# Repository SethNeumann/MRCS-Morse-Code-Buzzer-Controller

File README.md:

# REPO NAME: MRCS-Morse-Code-Buzzer-Controller
## License: Creative Commons Attribution-NonCommercial-ShareAlike

On many operations-oriented model railroads, particularly those which use time-table and train-order (TT&TO) or tower-based dispatching, 
there is a need to provide telephone communications between the dispatcher and the agent/operators. However, even on large model railroads
with multiple agent/operators, the physical distances between the operator positions are often insufficient to allow the operators to
reliably determine that “hey that’s my phone ringing.”

The Morse Code Buzzer Controller serves up to seven stations, tapping out each ringing station's Telegraph call sign in Railroad Morse.
An additional output can be designated an “ambience” buzzer that will randomly play one of several canned messages. These could be train
orders, news reports, or “inside jokes”

The board accepts push button inputs, stops when the phone goes off-hook (phone must have a suitable contact to provide an isolated ground 
or use the MRCS Off-Hook_Detector) and can drive loads of up to 0.5 Amp at up to 48 Volts DC.  All buzzer/sounder devices must use the same
supply.  Sounders must have have a coil resistance of greater than 40 ohms if using a 12V supply, or else use our Sounder Driver.

This version accepts 10-24 VDC from the MRCS telephone bus or a layout auxilliary supply or an external wall wart (not supplied)

The on-board Arduino Pro-Mini runs the "station buzzers" sketch by Steve Williams.  Please indicate the telegraph codes for your 
stations, unless you intend to load the sketch yourself.

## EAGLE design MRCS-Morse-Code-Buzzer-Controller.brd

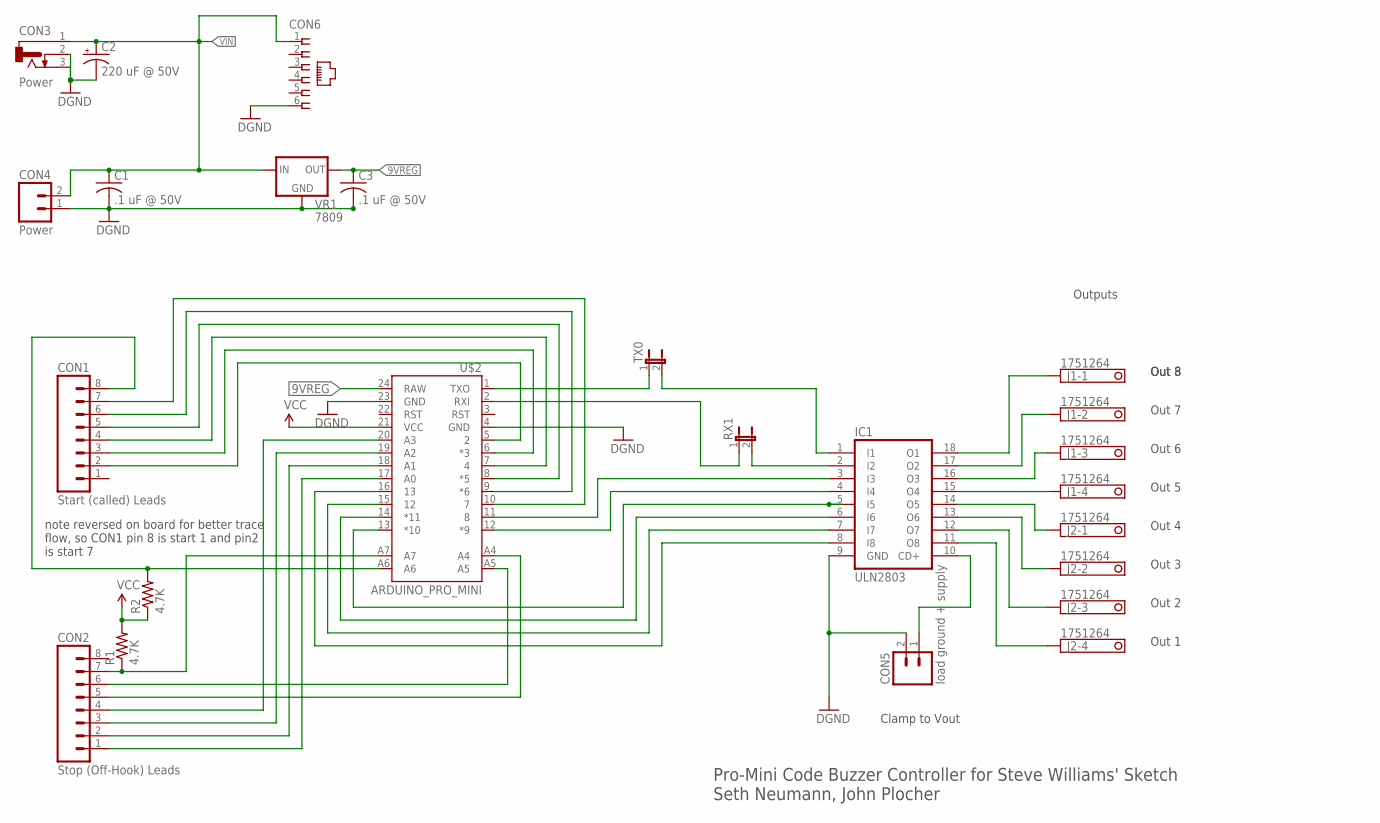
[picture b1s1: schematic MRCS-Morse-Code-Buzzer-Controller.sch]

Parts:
C1, C3: .1 uF @ 50V; C025-030X050
C2: 220 uF @ 50V; E3,5-10
CON1: Start (called) Leads; 1X08_LOCK
CON2: Stop (Off-Hook) Leads; 1X08_LOCK
CON3: Power; DCJ0202
CON4: Power; MSTB2
CON5: load ground + supply; MSTB2
CON6: CONNECTOR-RJ25-43860-2-MOLEX; RJ25-INVERTED
IC1: ULN2803; DIL18
J1, J2: 1751264
R1, R2: 4.7K; AXIAL-0.4-RES
RX1: JUMPER-2PTH; 1X02
TX0: JUMPER-2PTH; 1X02
U$2: ARDUINO_PRO_MINI
VR1: 7809; TO-220-RA-SINK

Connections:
9VREG: C3.1, U$2.24 (RAW), VR1.OUT
GND: C1.2, C2.-, C3.2, CON3.2, CON3.3, CON4.1, CON5.2, CON6.6, IC1.9 (GND), U$2.4 (GND), U$2.23 (GND), VR1.GND
unnamed: IC1.18 (O1), J1.1
unnamed: IC1.17 (O2), J1.2
unnamed: IC1.16 (O3), J1.3
unnamed: IC1.15 (O4), J1.4
unnamed: IC1.14 (O5), J2.1
unnamed: IC1.13 (O6), J2.2
unnamed: IC1.12 (O7), J2.3
unnamed: IC1.11 (O8), J2.4
unnamed: CON1.2, U$2.5 (2)
unnamed: CON1.3, U$2.6 (*3)
unnamed: CON1.4, U$2.7 (4)
unnamed: CON1.5, U$2.8 (*5)
unnamed: CON1.6, U$2.9 (*6)
unnamed: CON1.7, U$2.10 (7)
unnamed: CON1.8, R2.P$2 (2), U$2.A6
unnamed: CON2.7, R1.P$1 (1), U$2.A7
unnamed: CON2.1, U$2.17 (A0)
unnamed: IC1.3 (I3), U$2.11 (8)
unnamed: IC1.4 (I4), U$2.12 (*9)
unnamed: IC1.8 (I8), U$2.16 (13)
unnamed: IC1.5 (I5), U$2.13 (*10)
unnamed: IC1.6 (I6), U$2.14 (*11)
unnamed: IC1.7 (I7), U$2.15 (12)
unnamed: CON2.2, U$2.18 (A1)
unnamed: CON2.3, U$2.19 (A2)
unnamed: CON2.4, U$2.20 (A3)
unnamed: CON2.5, U$2.A4
unnamed: CON2.6, U$2.A5
unnamed: TX0.1, U$2.1 (TXO)
unnamed: IC1.1 (I1), TX0.2
unnamed: IC1.2 (I2), RX1.2
unnamed: CON5.1, IC1.10 (CD+)
unnamed: RX1.1, U$2.2 (RXI)
VCC: R1.P$2 (2), R2.P$1 (1), U$2.21 (VCC)
VIN: C1.1, C2.+, CON3.1, CON4.2, CON6.1, VR1.IN

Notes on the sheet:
Pro-Mini Code Buzzer Controller for Steve Williams' Sketch Seth Neumann, John Plocher
Outputs
Out 8
Out 7
Out 6
Out 5
Out 4
Out 3
Out 2
Out 1
note reversed on board for better trace flow, so CON1 pin 8 is start 1 and pin2 is start 7
Clamp to Vout

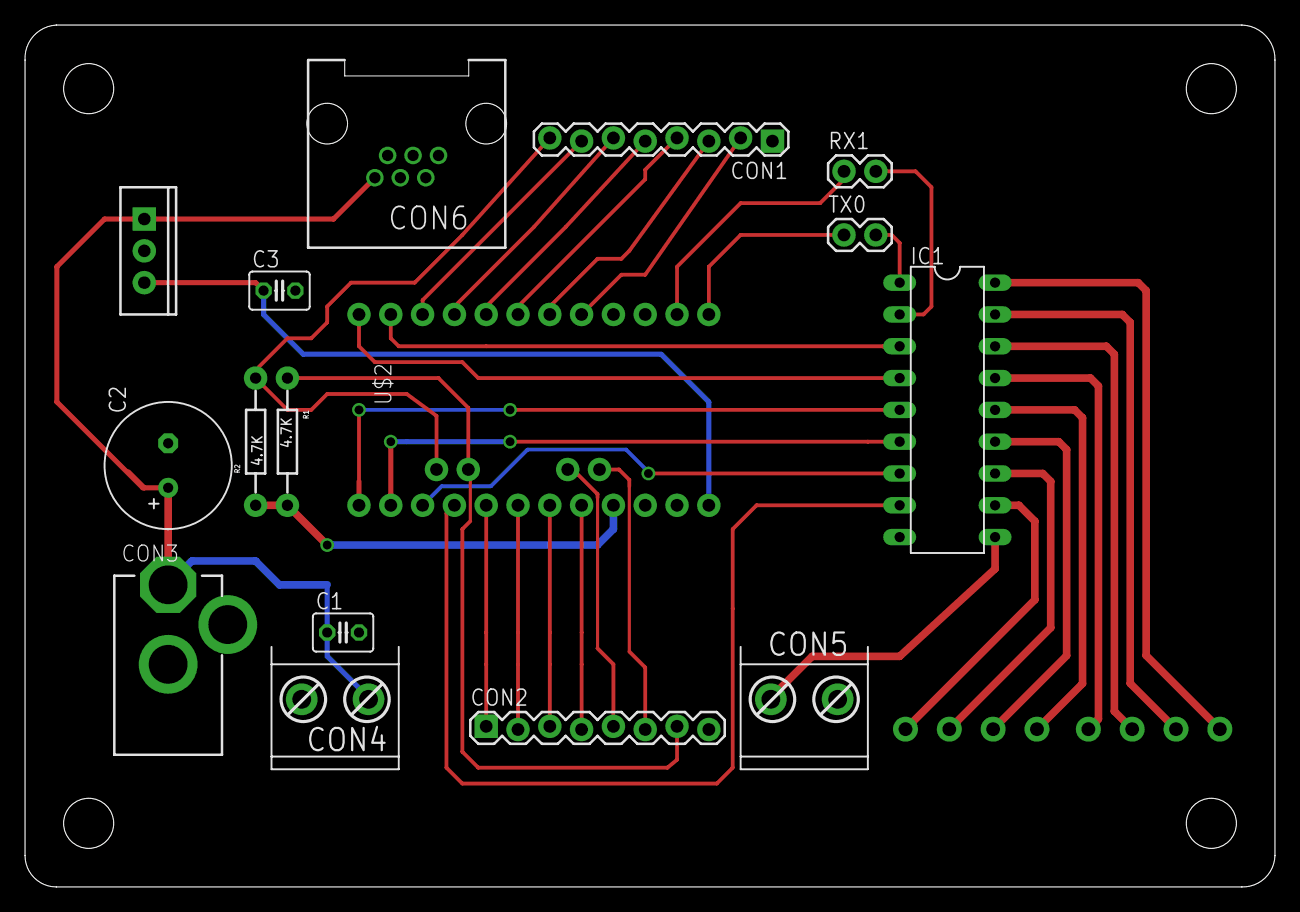
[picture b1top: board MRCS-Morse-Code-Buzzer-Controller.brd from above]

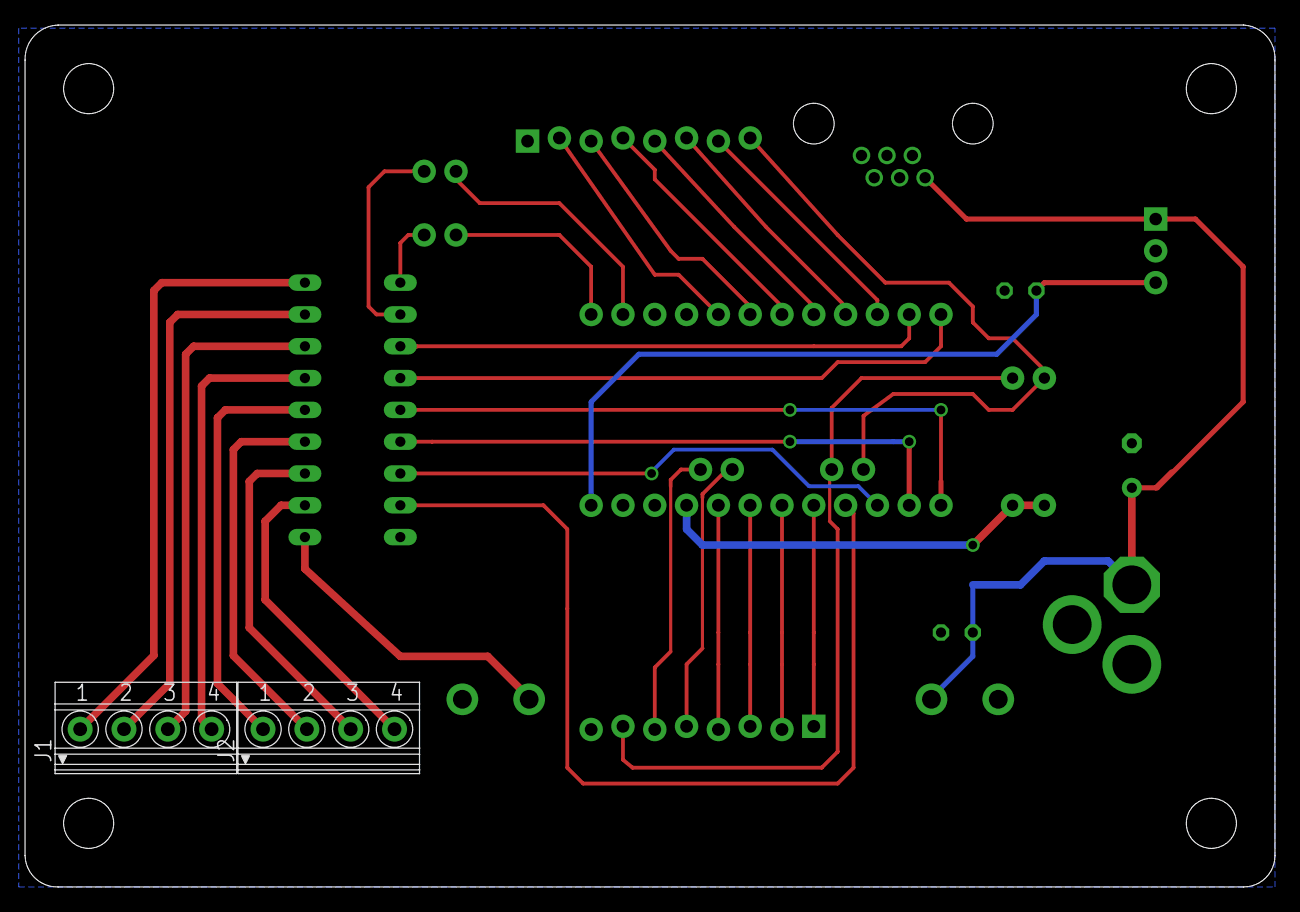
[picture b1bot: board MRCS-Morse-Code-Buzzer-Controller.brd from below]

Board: 2 copper layers, 99.8 x 68.8 mm, 20 parts (2 on the bottom side), 37 nets.

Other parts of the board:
U$1: BOARD-DINRAIL-2.71IN-MRCS
U$3: CA-PROP65WARNING

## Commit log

2020-09-30 initial commit
    initial commit
2020-09-30 spelling changes
2020-09-30 sent to fab
    sent to fab
2020-10-01 deleted dummy entries
    deleted dummy entries
2020-12-20 changes to gitignore
    cleaned out a bunch of work files and derivative files
2025-04-17 Create Morse Code Buzzer Controller Assembly and Installation.pdf
    Assembly and installation instructions. Apparently I never added this to the file.

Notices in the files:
parts and their libraries:
SparkFun-Boards-modified: Licensing: Creative Commons ShareAlike 4.0 International - https://creativecommons.org/licenses/by-sa/4.0
